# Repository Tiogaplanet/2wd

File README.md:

# 2wd

The two-wheeled robot with a low center of gravity.

**This repository contains the Eagle files for 2wd and a running log of its development.**

I like [MiP](https://github.com/Tiogaplanet/MiP_ESP8266_Library).  There's no denying the mobile inverted pendulum, for which it gets its name, is an innovative design.  Unfortunately the innovation comes at the cost of increased battery consumption.  MiP cannot come to a resting position as long as it is powered on.  In order to remain upright it must constantly rebalance itself to prevent from toppling over.

Other consumer grade robots such as Anki's [Vector](https://anki.com/en-us/vector.html) or [Cozmo](https://anki.com/en-us/cozmo.html) use a tracked design.  The many four-wheeled Arduino kits for sale around the Internet use skid steering similar to Vector and Cozmo at the cost of decreased agility compared to MiP's differential steering.  I'm looking for a different approach that has the agility of MiP but without the skid steering or complexity of a tracked or four-wheel drive system.

My solution is a robot with two parallel wheels, side by side, a layout known as a dicycle.  Technically, MiP fits this definition however I picture a design with the center of gravity below the horizontal center line of the wheels.  Such a design would conserve battery power when the robot is at rest.

I have found only a couple notable examples of such a design online.  [Parrot's Sumo](https://www.parrot.com/us/minidrones/parrot-jumping-sumo) fits the description but it appears to be dragging a solid tail to counter torque and keep the robot upright.  The best example I've seen of a self-balancing dicycle comes from [Simon Winder](http://simonwinder.com/2015/06/two-wheeled-rolling-robot/).  Winder's robot uses an inertial measurement unit (IMU) to keep the body upright and it uses infrared to avoid obstacles.

I propose developing a robot similar to Winder's, built around the Arduino Nano 33 IoT, which has an integrated six-degree IMU along with WiFi and Bluetooth.  The robot will also include an on-board battery management system, IR detection, an OLED display and eventually a camera.

I'll update the bill of materials for prototyping as I develop the robot.  For now it looks like this:

| Description | Quantity |
|-------------|----------|
| [Arduino Nano 33 IoT](https://store.arduino.cc/usa/nano-33-iot) | 1 |
| 15 pin female headers for Nano | 2 |
| [90x10mm wheels](https://www.pololu.com/product/1435) | 2 |
| [Gear motors](https://www.pololu.com/product/1520) | 2 |
| [Gear motor bracket pair](https://www.pololu.com/product/2681) | 1 |
| [Magnetic encoder pair](https://www.pololu.com/product/1523) | 1 |
| [Motor driver](https://www.pololu.com/product/2135) | 1 |
| 7 pin female headers for driver | 2 |
| [IR sensors](https://www.pololu.com/product/2476) | 2 |
| [Battery management system (BMS)](https://www.amazon.com/gp/product/B07S7PKPH6/ref=ppx_yo_dt_b_asin_title_o03_s00?ie=UTF8&psc=1) | 1 |
| [Prototype board (7x9 cm) for motherboard and drive/power board](https://www.amazon.com/gp/product/B072Z7Y19F/ref=ppx_yo_dt_b_asin_title_o04_s01?ie=UTF8&psc=1) | 2 |
| 18650 batteries | 2 |
| [Voltage regulator](https://www.amazon.com/gp/product/B00IJYDJTS/ref=ppx_yo_dt_b_search_asin_title?ie=UTF8&psc=1) | 1 |
| 15mm PCB stand-offs, nuts and screws for regulator | 2 |
| [DC barrel jack](https://www.amazon.com/gp/product/B074LK7G86/ref=ppx_yo_dt_b_asin_title_o04_s00?ie=UTF8&psc=1) | 1 |
| [SPDT switch](https://www.ebay.com/itm/12-Breadboard-slide-switches-3-pin-50-volt-500-milliamp-SPDT-switch-Arduino/112891316956) | 1 |
| 26mm PCB stand-offs, nuts and screws for motherboard and drive/power board | 4 |
| [OLED display](https://www.amazon.com/gp/product/B072Q2X2LL/ref=ppx_yo_dt_b_search_asin_title?ie=UTF8&psc=1) | 1 |
| PCB stand-offs, nuts and screws for OLED display | 4 |

## 24 December 2019

I spent today finishing the power circuit and moving the motor controller and Nano onto the chassis.  I set the voltage regulator module output to 5.1 volts.  That will provide enough juice to power both motors.  The voltage regulator onboard the Nano (VIN) will get it down to the 3.3 volts required by the Nano 33 IoT.  

This first picture shows the voltage regulator module connected to the BMS.  I used a simple jumper as an on/off switch to conserve space on the board while I ponder a better solution.  The output of the voltage regulator is connected to the prototype board so that I can pass power to the top board where the Nano and motor controller are soldered.

After some debugging in software I got the thing working.  I found that my check for an established serial connection would cause the entire sketch to hang when the robot was finally untethered from the computer.

Next steps are to implement PID in the library to keep the body level while moving and get the IR sensors working.

## 21 December 2019

Spent a few hours tonight soldering up the batteries, BMS and barrel jack.  The picture below shows  everything together.

The next picture shows a test fit of the voltage regulator.  I am holding off on installing the voltage regulator until I decide what kind of power switch to use.  The motors have a peak draw of 1.2 amps.  Because of that I'm debating a plain old SPDT switch or a MOSFET-based switch circuit.

I was concerned that this robot would be made up of too many modular circuits like the voltage regulator, but seeing how nicely it fits made me glad I decided to use it instead of assembling my own regulator circuit from scratch.

## 19 December 2019

No new work.  Just sharing some of my latest pictures.  Below is a picture of 2wd doing some bench testing.  It's sitting on the box for the Nano 33 IoT while I test code for operating the motors.  I'm using the Arduino Uno clone behind the breadboard to power the motors.  The motors still need more current than what the Uno clone provides.  However, I have received some 2.1mm DC barrel jacks in the mail so I will be able to connect a wall-wart power supply to the motors via the LM2596 module.

I soldered a few right-angle pins onto the BMS to make it fit onto the prototyping board that makes up 2wd's chassis.  I didn't use a lot of solder in case I needed to undo it.  Once everything tests out I'll do come back and re-solder the right-angle pins.

The LM2596 module doesn't plug into a prototyping board either but it has screw holes so I plan to drill holes in the prototyping board and mount the module using PCB stand-offs.

## 13 December 2019

The last several weeks I have tried organizing a place to work in my latest home.  Today I was finally able to assemble a few things.

Not shown in the pictures above is a "motherboard" mounted above the gear motors using PCB stand-offs in the pre-drilled holes of the prototyping board.  I realized quickly that I did not have enough space to mount the Nano, OLED display and pretty much anything else after securing the gear motors and batteries to the drive/power board.  While this will make the body of the robot taller, it will still be within the diameter of the wheels and won't come close to offsetting the weight of the batteries.  It should also reduce body flex between the two wheels.

I have breadboard-tested the motor driver using pulse-width modulation in a simple sketch.  The wheels turn forward together at a medium speed before momentarily stopping, then turning backward.  In the same sketch I also tested the use of an OLED display.  So far, so good.  Although, I still need to develop an [actual library](https://github.com/Tiogaplanet/2wd_library) to drive the robot.

Next, I plan to sort out the power and charging system.  I have soldered right-angle pins to the BMS to make it "breadboard friendly."  It will sit close to the prototype board so for now I plan to install it underneath the robot, between the batteries with the voltage regulator stacked below it using PCB stand-offs. Now I'm just waiting for the barrel jack and power switch to arrive in the mail before I assemble anything else.

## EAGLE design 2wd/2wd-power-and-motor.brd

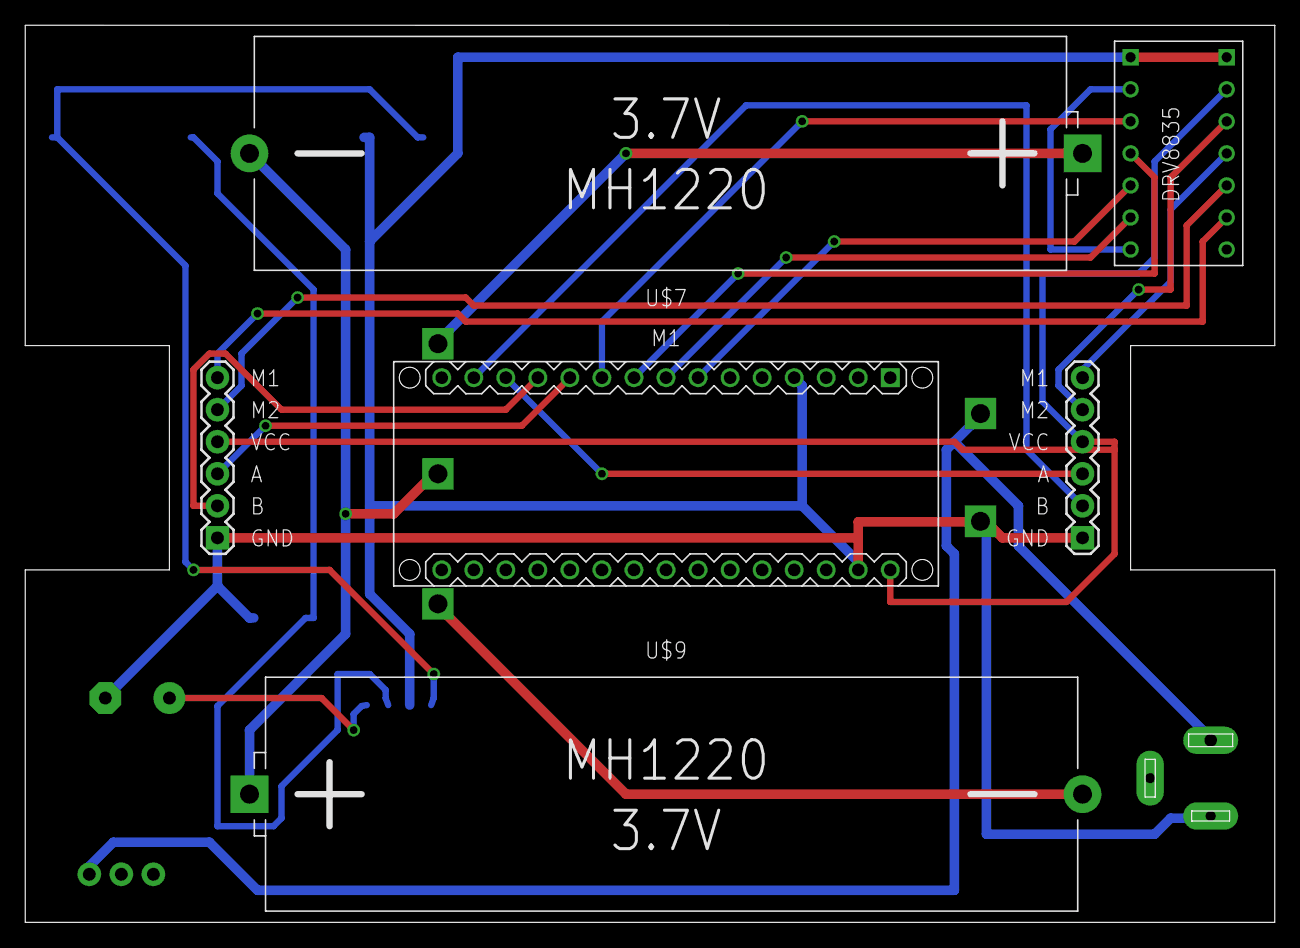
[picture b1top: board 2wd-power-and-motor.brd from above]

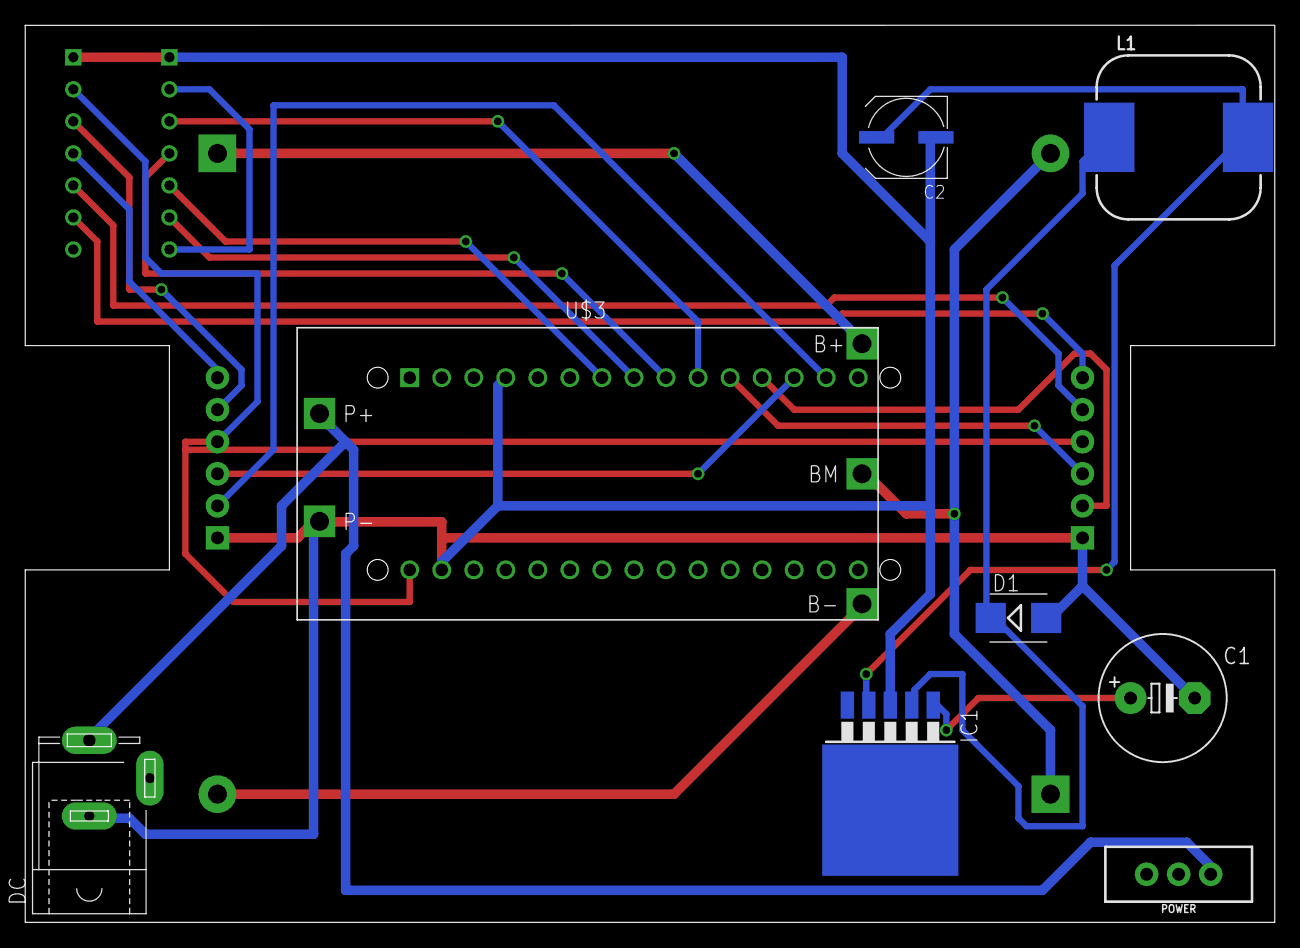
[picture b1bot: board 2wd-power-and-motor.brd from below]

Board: 2 copper layers, 99.1 x 71.1 mm, 15 parts (8 on the bottom side), 22 nets.

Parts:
C1: 680uF; E5-10,5
C2: 220uF; UD-6,3X5,8_NICHICON
D1: 1N5824; SMB
DC: 9V; SPC4077
FRAME1: FRAME-LETTER; CREATIVE_COMMONS
IC1: LM2596S; TO263-5
J1: LEFT_MOTOR_CONN
J5: RIGHT_MOTOR_CONN
L1: CDRH127/LD
M1: ARDUINO-NANO-3.0-SOCKET
POWER: SWITCH_SPDT_PTH_11.6X4.0MM
U$2: POLOLU_MOTOR_DRV8835THROUGHHOLE; POLOLU_MOTOR_DRV_DRV8835
U$3: BATTERY-MANAGEMENT-SYSTEM
U$7, U$9: BATTERY-LI-MH12210

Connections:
+5V: J1.4, J5.4, M1.J2.1, U$2.VIN
AENBL: M1.J1.7, U$2.AENBL
APHASE: M1.J1.8, U$2.APHASE
BENBL: M1.J1.10, U$2.BENBL
BPHASE: M1.J1.9, U$2.BPHASE
FB: C2.+, IC1.4, L1.2
GND: C1.-, C2.-, D1.A, DC.1, IC1.3, J1.1, J5.1, M1.J1.4, M1.J2.2, U$2.LGND, U$2.MGND, U$3.P-
LA: J1.3, M1.J1.11
LB: J1.2, M1.J1.12
LM1: J1.6, U$2.AOUT1
LM2: J1.5, U$2.AOUT2
unnamed: DC.3, POWER.3, U$3.P+
unnamed: U$3.B+, U$7.BAT+
unnamed: U$3.B-, U$9.BAT-
unnamed: U$3.BM, U$7.BAT-, U$9.BAT+
unnamed: U$2.MODE, U$2.VCC
OUT: D1.C, IC1.2, L1.1
RA: J5.3, M1.J1.13
RB: J5.2, M1.J1.14
RM1: J5.6, U$2.BOUT1
RM2: J5.5, U$2.BOUT2
VIN1: C1.+, IC1.1

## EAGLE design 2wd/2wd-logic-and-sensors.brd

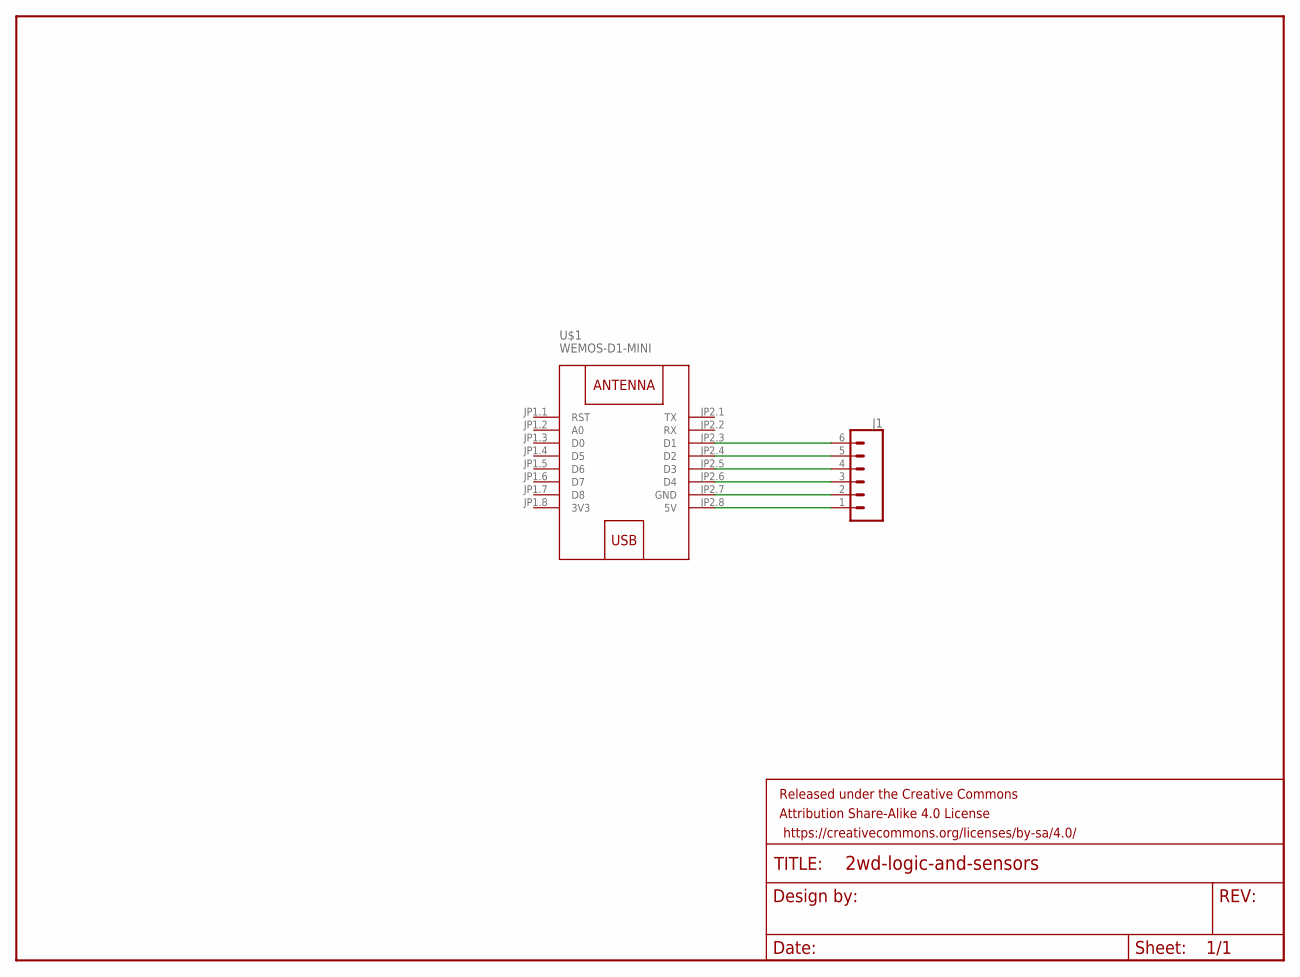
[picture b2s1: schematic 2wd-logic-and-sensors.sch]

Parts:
FRAME1: FRAME-LETTER; CREATIVE_COMMONS
J1: CONN_06NO_SILK_FEMALE_PTH; 1X06_NO_SILK
U$1: WEMOS-D1-MINI

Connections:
3V3: U$1.JP1.8 (3V3)
unnamed: J1.1, U$1.JP2.8 (5V)
unnamed: J1.2, U$1.JP2.7 (GND)
unnamed: J1.3, U$1.JP2.6 (D4)
unnamed: J1.4, U$1.JP2.5 (D3)
unnamed: J1.5, U$1.JP2.4 (D2)
unnamed: J1.6, U$1.JP2.3 (D1)

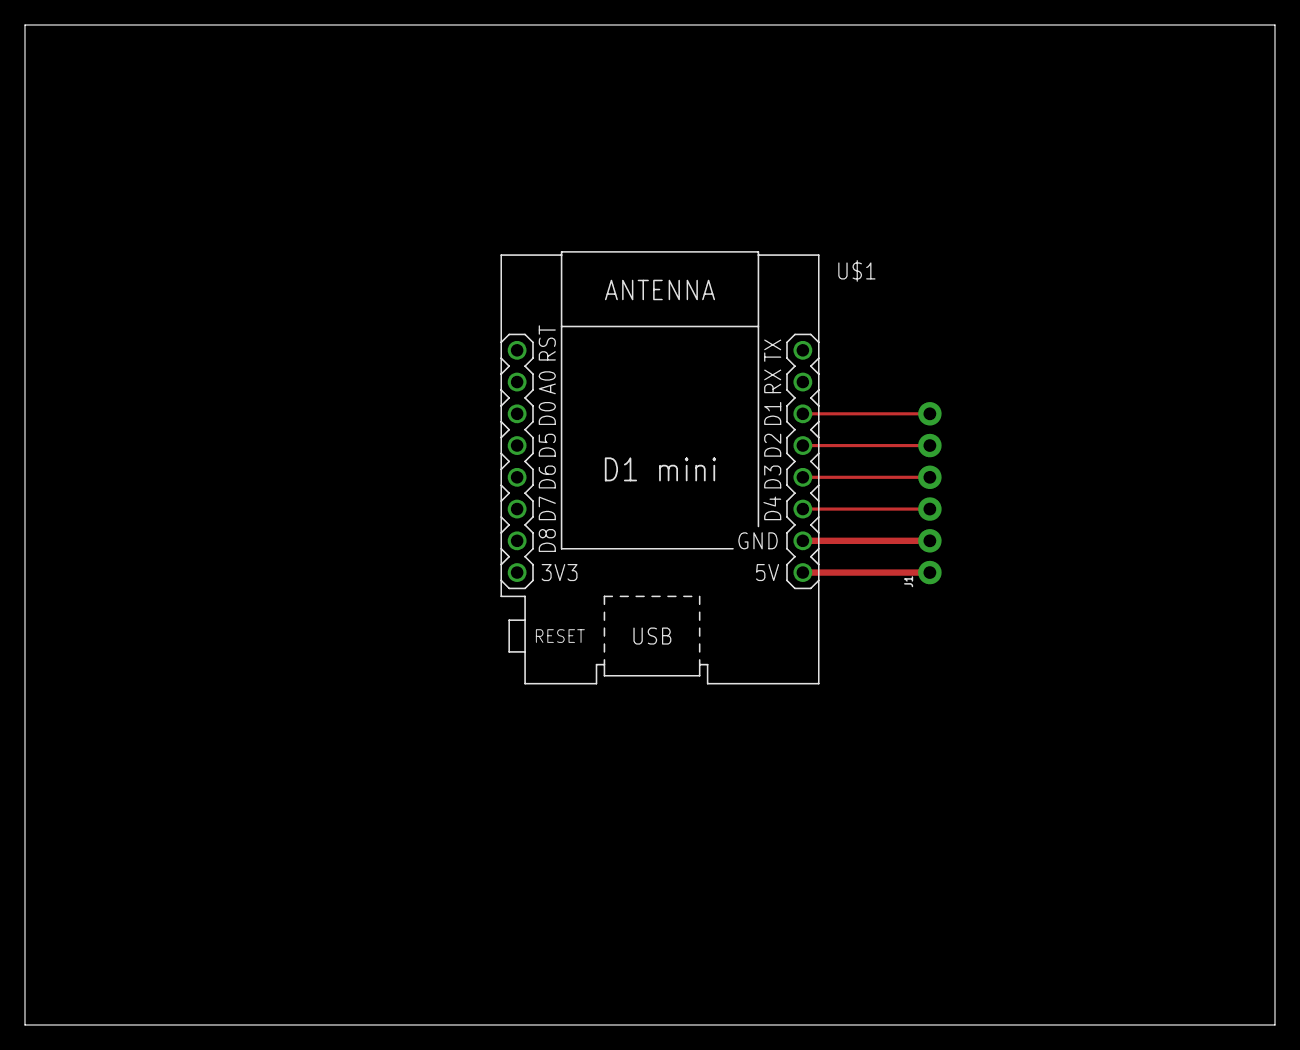
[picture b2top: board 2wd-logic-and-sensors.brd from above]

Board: 2 copper layers, 100.0 x 80.0 mm, 3 parts (0 on the bottom side), 6 nets.

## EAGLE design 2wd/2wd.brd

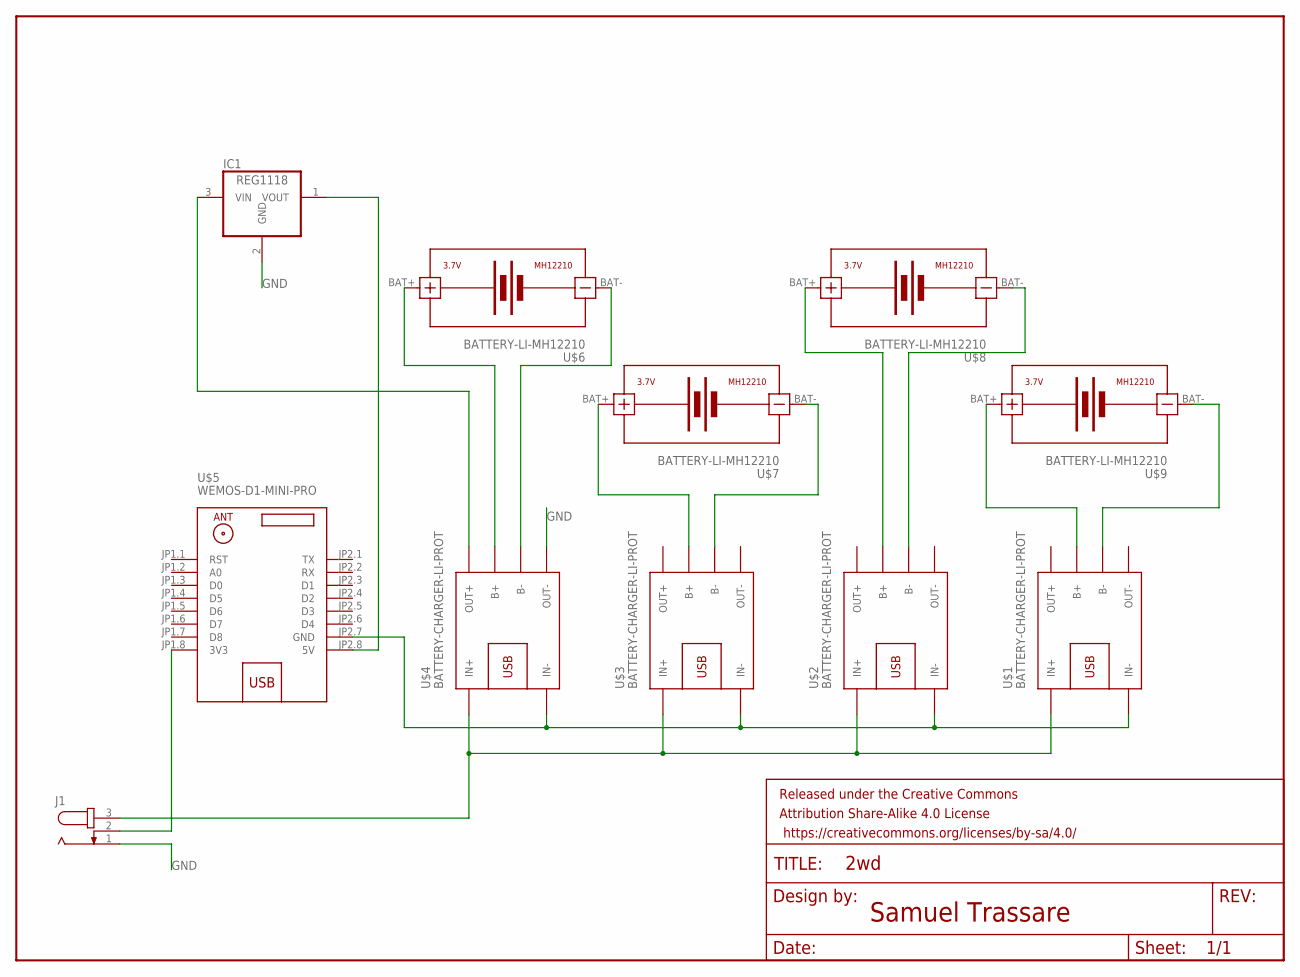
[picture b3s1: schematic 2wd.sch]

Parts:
FRAME1: FRAME-LETTER; CREATIVE_COMMONS
IC1: REG1118; SOT223
J1: JACK-PLUG0; SPC4077
U$1, U$2, U$3, U$4: BATTERY-CHARGER-LI-PROT
U$5: WEMOS-D1-MINI-PRO
U$6, U$7, U$8, U$9: BATTERY-LI-MH12210

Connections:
GND: IC1.2 (GND), J1.1, U$1.IN-, U$2.IN-, U$3.IN-, U$4.IN-, U$4.OUT-, U$5.JP2.7 (GND)
unnamed: U$1.B-, U$9.BAT-
unnamed: U$2.B-, U$8.BAT-
unnamed: U$3.B-, U$7.BAT-
unnamed: U$4.B-, U$6.BAT-
unnamed: U$3.B+, U$7.BAT+
unnamed: U$2.B+, U$8.BAT+
unnamed: U$1.B+, U$9.BAT+
unnamed: U$4.B+, U$6.BAT+
unnamed: IC1.3 (VIN), U$4.OUT+
unnamed: IC1.1 (VOUT), U$5.JP2.8 (5V)
unnamed: J1.2, U$5.JP1.8 (3V3)
VCC: J1.3, U$1.IN+, U$2.IN+, U$3.IN+, U$4.IN+

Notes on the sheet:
Samuel Trassare

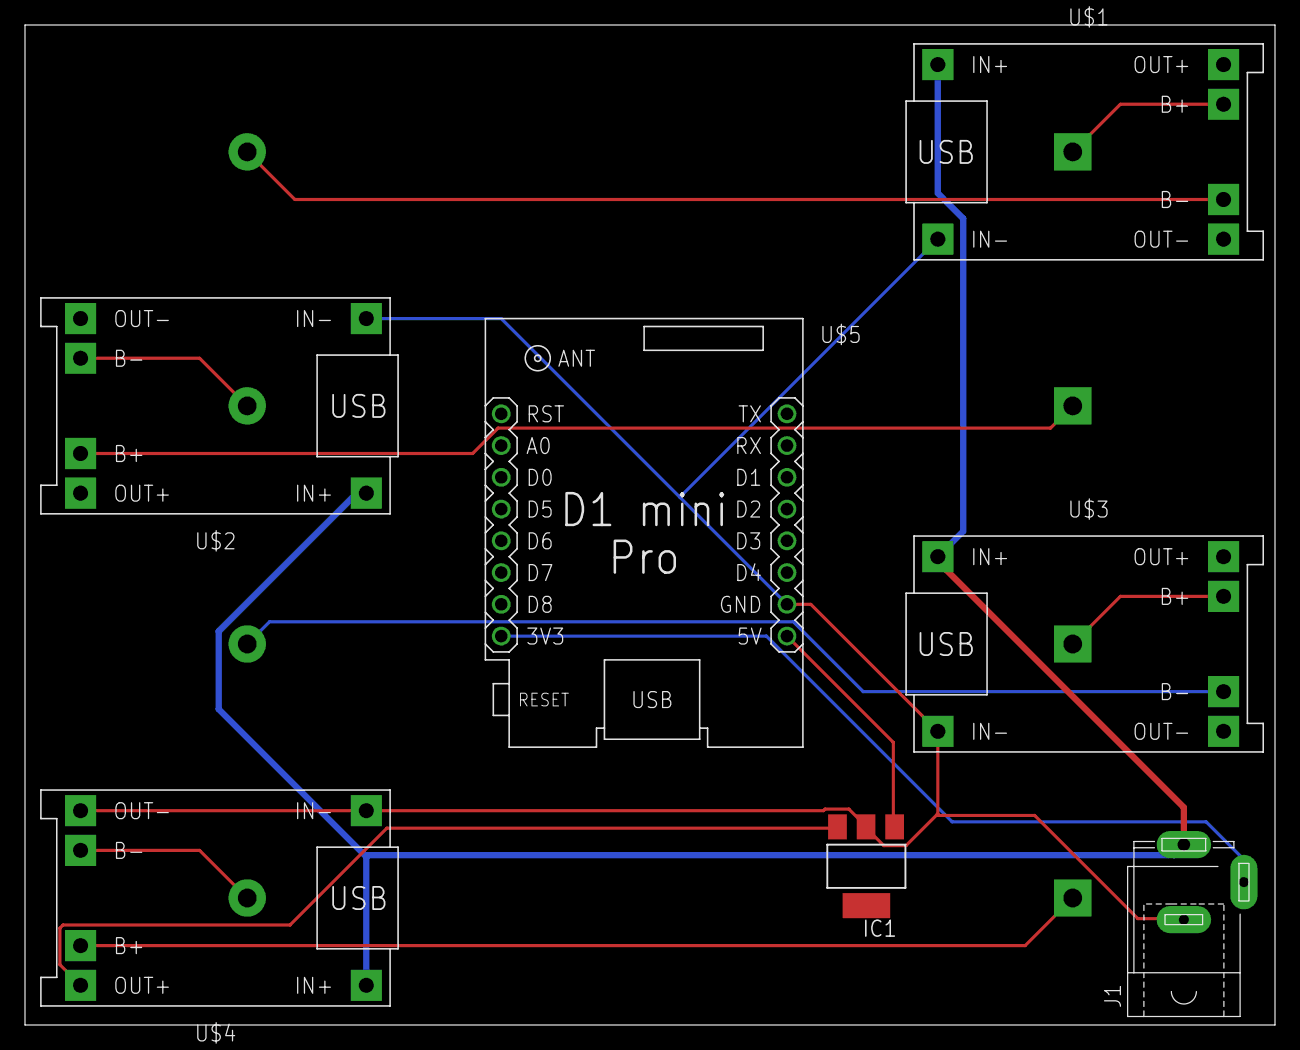
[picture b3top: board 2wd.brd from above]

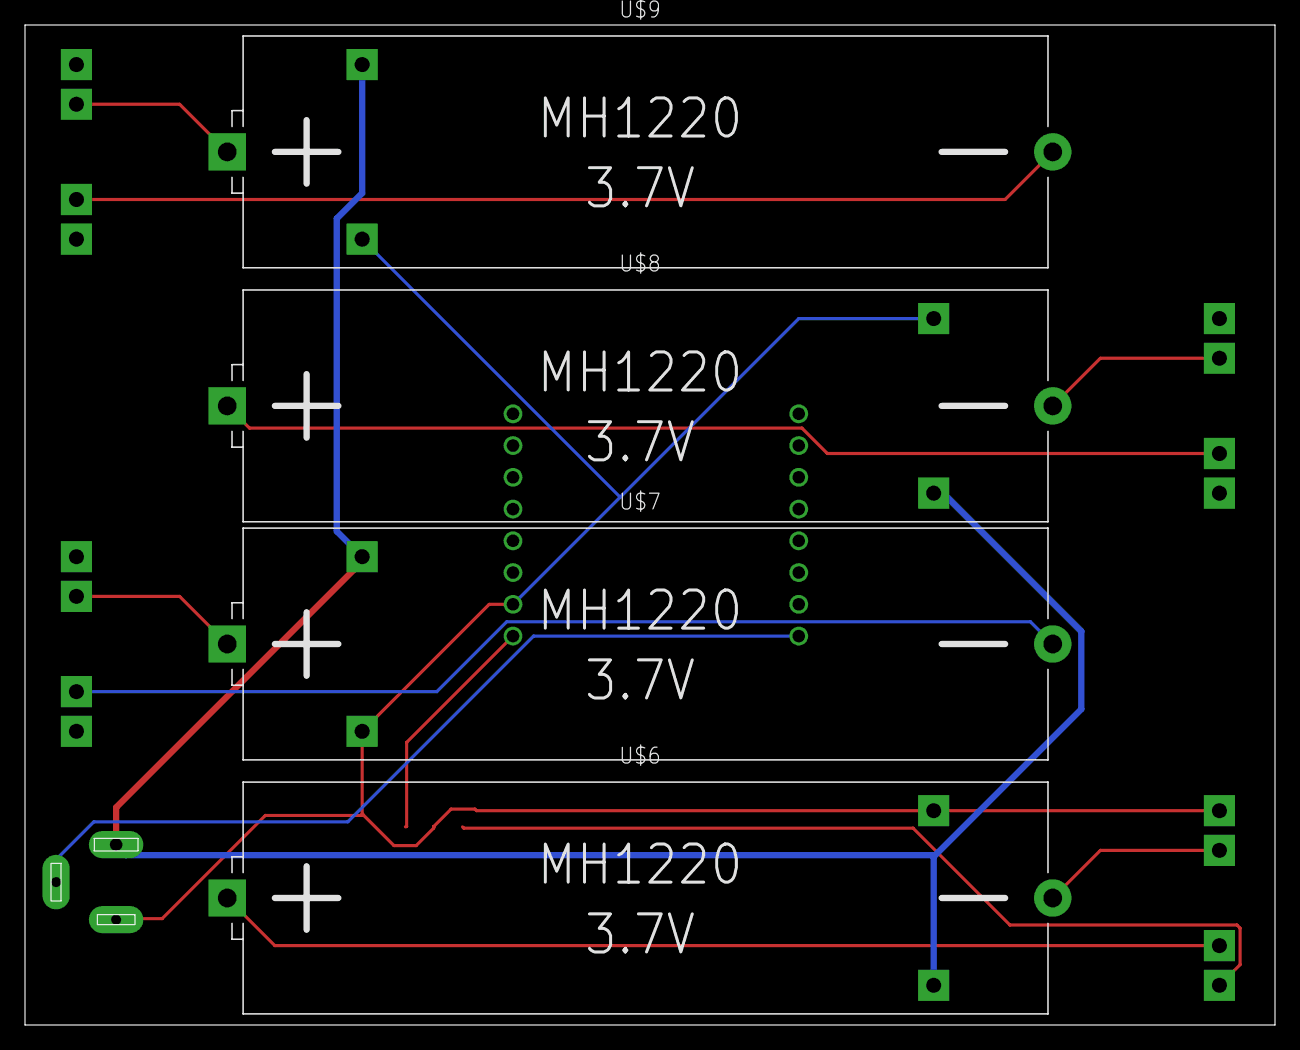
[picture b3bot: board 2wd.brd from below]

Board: 2 copper layers, 100.0 x 80.0 mm, 12 parts (4 on the bottom side), 13 nets.

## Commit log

2019-10-24 Initial eagle files
2019-10-24 Start adding power control
2019-10-28 Created two boards in Eagle.
    Finally decided to create two boards within one Eagle project. A motherboard and a power management/motor controller daughterboard.
2019-10-29 Resized board, added motor driver.
2019-10-30 Added integrated voltage regulation
2019-12-14 Added pictures of the build.
    Added pictures of the build and updated the readme.
2019-12-17 Expound upon the diary entry, clarify the readme.
    Original update was short because I didn't have a lot of type to write a good, thorough entry. I've come back and expounded upon the weekend's work and update the BOM and my way ahead.
2019-12-17 Added a "bottom line up front."
2019-12-19 Added some more pics.
2019-12-19 Added update with photos.
2019-12-19 Fixed the stand-off sizes.
    Still need to measure stand-offs for the OLED display.
2019-12-22 Charging circuit
2019-12-22 copy paste error
2019-12-24 assembled
2019-12-26 Added some detail to yesterday's work.
2019-12-26 forgot to save last edit.

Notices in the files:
parts and their libraries:
SparkFun-Aesthetics: Licensing: Creative Commons ShareAlike 4.0 International - https://creativecommons.org/licenses/by-sa/4.0
SparkFun-Aesthetics: Released under the Creative Commons Attribution Share-Alike 4.0 License
SparkFun-Aesthetics: https://creativecommons.org/licenses/by-sa/4.0
